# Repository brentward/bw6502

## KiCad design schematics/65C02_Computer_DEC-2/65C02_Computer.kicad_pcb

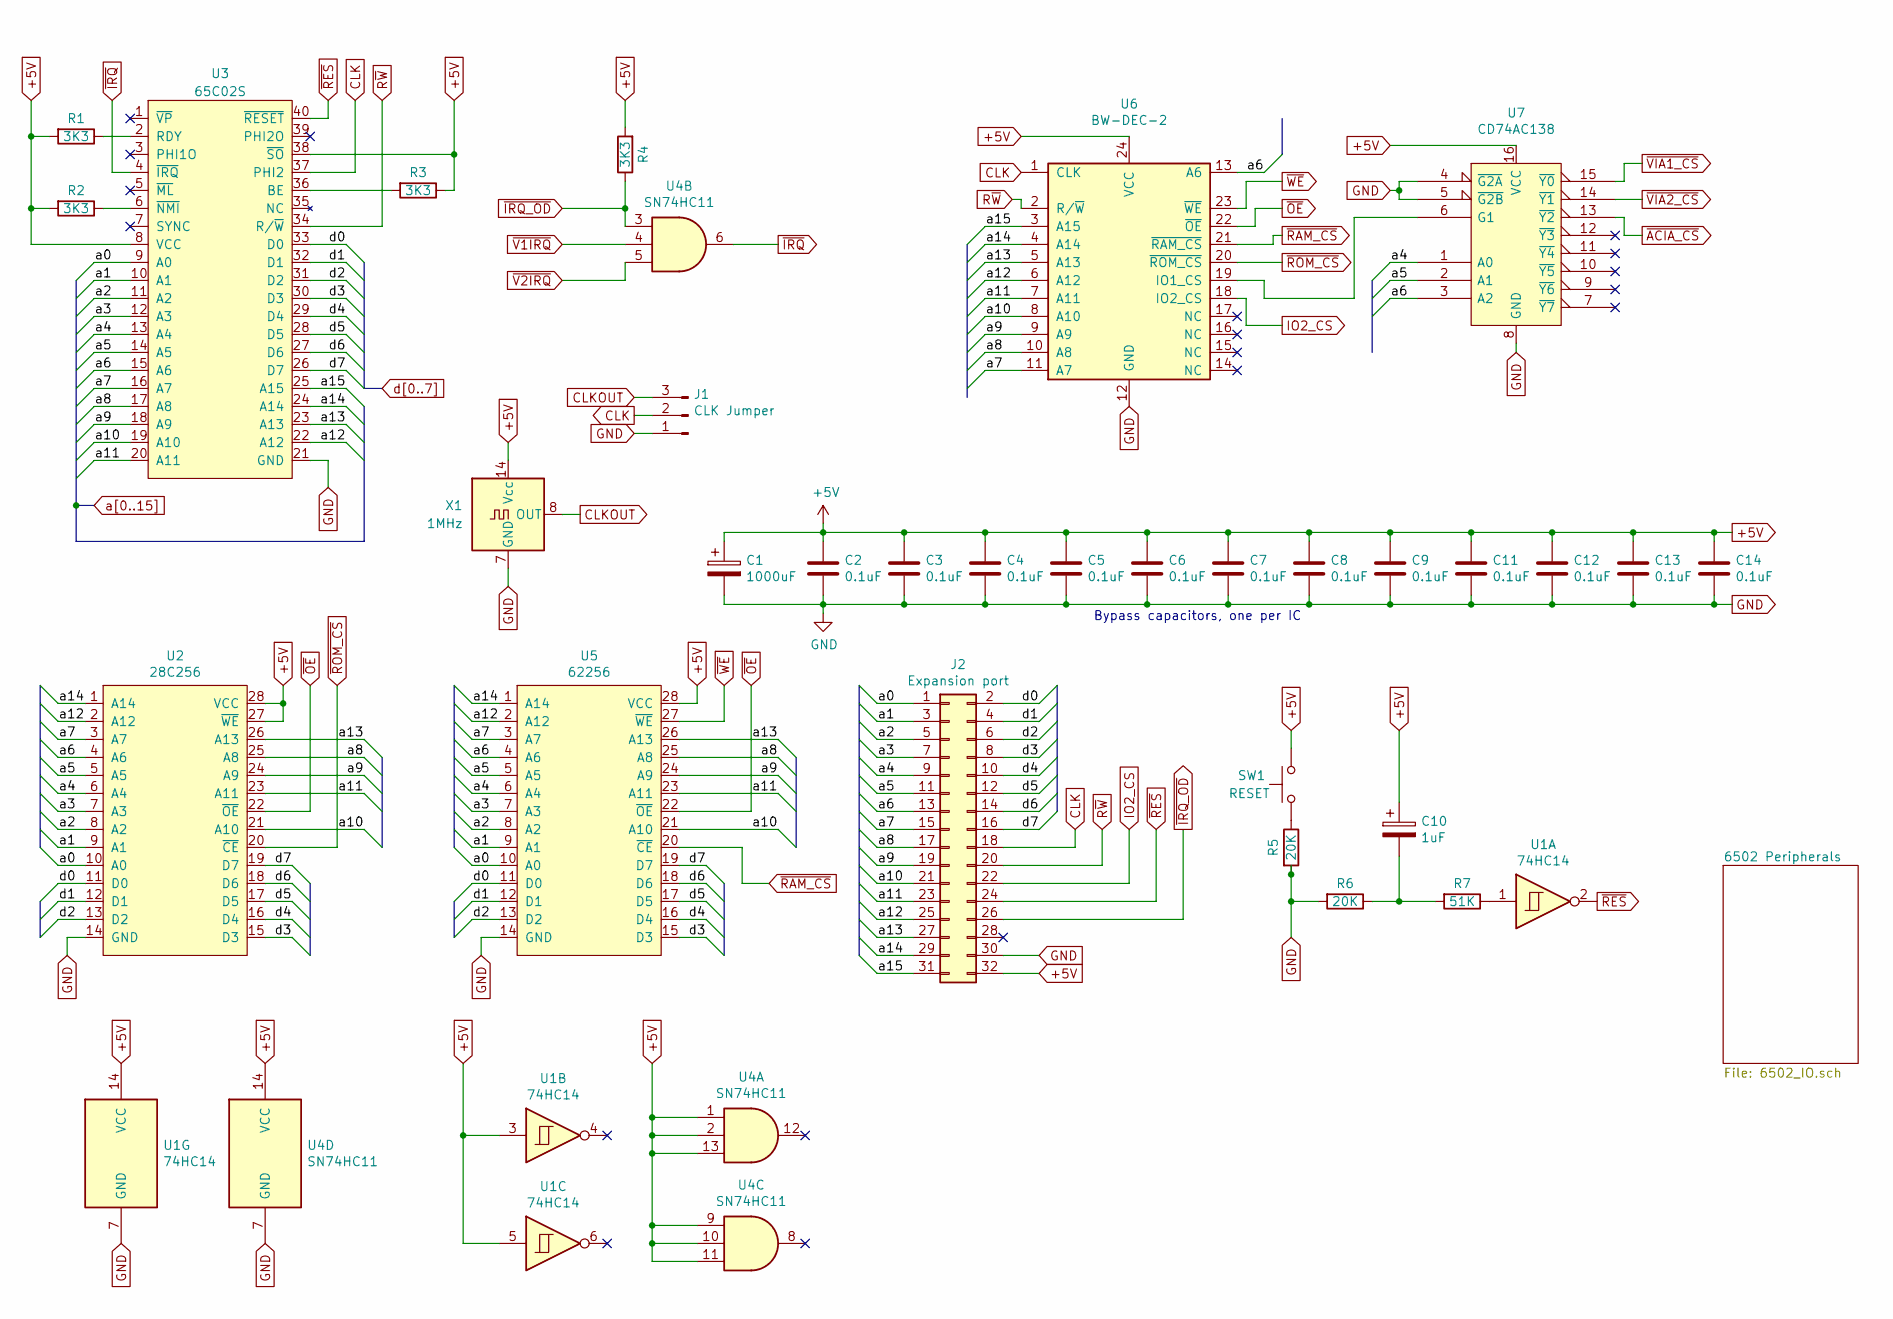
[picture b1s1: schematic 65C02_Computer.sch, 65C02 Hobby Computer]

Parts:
C1: 1000uF; CP_Radial_D10.0mm_P5.00mm
C2, C3, C4, C5, C6, C7, C8, C9, C11, C12, C13, C14: 0.1uF; C_Disc_D3.4mm_W2.1mm_P2.50mm
C10: 1uF; CP_Radial_D5.0mm_P2.50mm
J1: CLK Jumper; PinHeader_1x03_P2.54mm_Vertical
J2: Expansion port; PinSocket_2x16_P2.54mm_Vertical
R1, R2, R3, R4: 3K3; R_Axial_DIN0207_L6.3mm_D2.5mm_P7.62mm_Horizontal
R5, R6: 20K; R_Axial_DIN0207_L6.3mm_D2.5mm_P7.62mm_Horizontal
R7: 51K; R_Axial_DIN0207_L6.3mm_D2.5mm_P7.62mm_Horizontal
SW1: RESET; SW_PUSH_6mm_H4.3mm
U1: 74HC14; DIP-14_W7.62mm
U2: 28C256; DIP-28_W15.24mm_Socket
U3: 65C02S; DIP-40_W15.24mm_Socket
U4: SN74HC11; DIP-14_W7.62mm
U5: 62256; DIP-28_W15.24mm_Socket
U6: BW-DEC-2; DIP-24_W7.62mm_Socket
U7: CD74AC138; DIP-16_W7.62mm
X1: 1MHz; Oscillator_DIP-14

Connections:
+5V: C1.1, C2.1, C3.1, C4.1, C5.1, C6.1, C7.1, C8.1, C9.1, C10.1, C11.1, C12.1, C13.1, C14.1, J2.32, R1.2, R2.2, R3.1, R4.2, SW1.2, U1.3, U1.5, U1.14 (VCC), U2.27 (~WE), U2.28 (VCC), U3.8 (VCC), U3.38 (~SO), U4.1, U4.2, U4.9, U4.10, U4.11, U4.13, U4.14 (VCC), U5.28 (VCC), U6.24 (VCC), U7.16 (VCC), X1.14 (Vcc); also elsewhere on the board
CLK: J1.2, J2.18, U3.37 (PHI2), U6.1 (CLK); also elsewhere on the board
CLKOUT: J1.3, X1.8 (OUT)
GND: C1.2, C2.2, C3.2, C4.2, C5.2, C6.2, C7.2, C8.2, C9.2, C11.2, C12.2, C13.2, C14.2, J1.1, J2.30, R5.2, R6.2, U1.7 (GND), U2.14 (GND), U3.21 (GND), U4.7 (GND), U5.14 (GND), U6.12 (GND), U7.4 (~G2A), U7.5 (~G2B), U7.8 (GND), X1.7 (GND); also elsewhere on the board
IO2_CS: J2.22, U6.18 (IO2_CS)
unnamed: C10.2, R6.1, R7.2
unnamed: R1.1, U3.2 (RDY)
unnamed: R2.1, U3.6 (~NMI)
unnamed: R3.2, U3.36 (BE)
unnamed: R5.1, SW1.1
unnamed: R7.1, U1.1
unnamed: U6.19 (IO1_CS), U7.6 (G1)
R~W: J2.20, U3.34 (R/~W), U6.2 (R/~W); also elsewhere on the board
a0: J2.1, U2.10 (A0), U3.9 (A0), U5.10 (A0); also elsewhere on the board
a1: J2.3, U2.9 (A1), U3.10 (A1), U5.9 (A1); also elsewhere on the board
a2: J2.5, U2.8 (A2), U3.11 (A2), U5.8 (A2); also elsewhere on the board
a3: J2.7, U2.7 (A3), U3.12 (A3), U5.7 (A3); also elsewhere on the board
a4: J2.9, U2.6 (A4), U3.13 (A4), U5.6 (A4), U7.1 (A0)
a5: J2.11, U2.5 (A5), U3.14 (A5), U5.5 (A5), U7.2 (A1)
a6: J2.13, U2.4 (A6), U3.15 (A6), U5.4 (A6), U6.13 (A6), U7.3 (A2)
a7: J2.15, U2.3 (A7), U3.16 (A7), U5.3 (A7), U6.11 (A7)
a8: J2.17, U2.25 (A8), U3.17 (A8), U5.25 (A8), U6.10 (A8)
a9: J2.19, U2.24 (A9), U3.18 (A9), U5.24 (A9), U6.9 (A9)
a10: J2.21, U2.21 (A10), U3.19 (A10), U5.21 (A10), U6.8 (A10)
a11: J2.23, U2.23 (A11), U3.20 (A11), U5.23 (A11), U6.7 (A11)
a12: J2.25, U2.2 (A12), U3.22 (A12), U5.2 (A12), U6.6 (A12)
a13: J2.27, U2.26 (A13), U3.23 (A13), U5.26 (A13), U6.5 (A13)
a14: J2.29, U2.1 (A14), U3.24 (A14), U5.1 (A14), U6.4 (A14)
a15: J2.31, U3.25 (A15), U6.3 (A15)
d0: J2.2, U2.11 (D0), U3.33 (D0), U5.11 (D0); also elsewhere on the board
d1: J2.4, U2.12 (D1), U3.32 (D1), U5.12 (D1); also elsewhere on the board
d2: J2.6, U2.13 (D2), U3.31 (D2), U5.13 (D2); also elsewhere on the board
d3: J2.8, U2.15 (D3), U3.30 (D3), U5.15 (D3); also elsewhere on the board
d4: J2.10, U2.16 (D4), U3.29 (D4), U5.16 (D4); also elsewhere on the board
d5: J2.12, U2.17 (D5), U3.28 (D5), U5.17 (D5); also elsewhere on the board
d6: J2.14, U2.18 (D6), U3.27 (D6), U5.18 (D6); also elsewhere on the board
d7: J2.16, U2.19 (D7), U3.26 (D7), U5.19 (D7); also elsewhere on the board
~ACIA_CS: U7.13 (~Y2); also elsewhere on the board
~IRQ: U3.4 (~IRQ), U4.6
~IRQ_OD: J2.26, R4.1, U4.3; also elsewhere on the board
~OE: U2.22 (~OE), U5.22 (~OE), U6.22 (~OE)
~RAM_CS: U5.20 (~CE), U6.21 (~RAM_CS)
~RES: J2.24, U1.2, U3.40 (~RESET); also elsewhere on the board
~ROM_CS: U2.20 (~CE), U6.20 (~ROM_CS)
~V1IRQ: U4.4; also elsewhere on the board
~V2IRQ: U4.5; also elsewhere on the board
~VIA1_CS: U7.15 (~Y0); also elsewhere on the board
~VIA2_CS: U7.14 (~Y1); also elsewhere on the board
~WE: U5.27 (~WE), U6.23 (~WE)

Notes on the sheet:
Bypass capacitors, one per IC

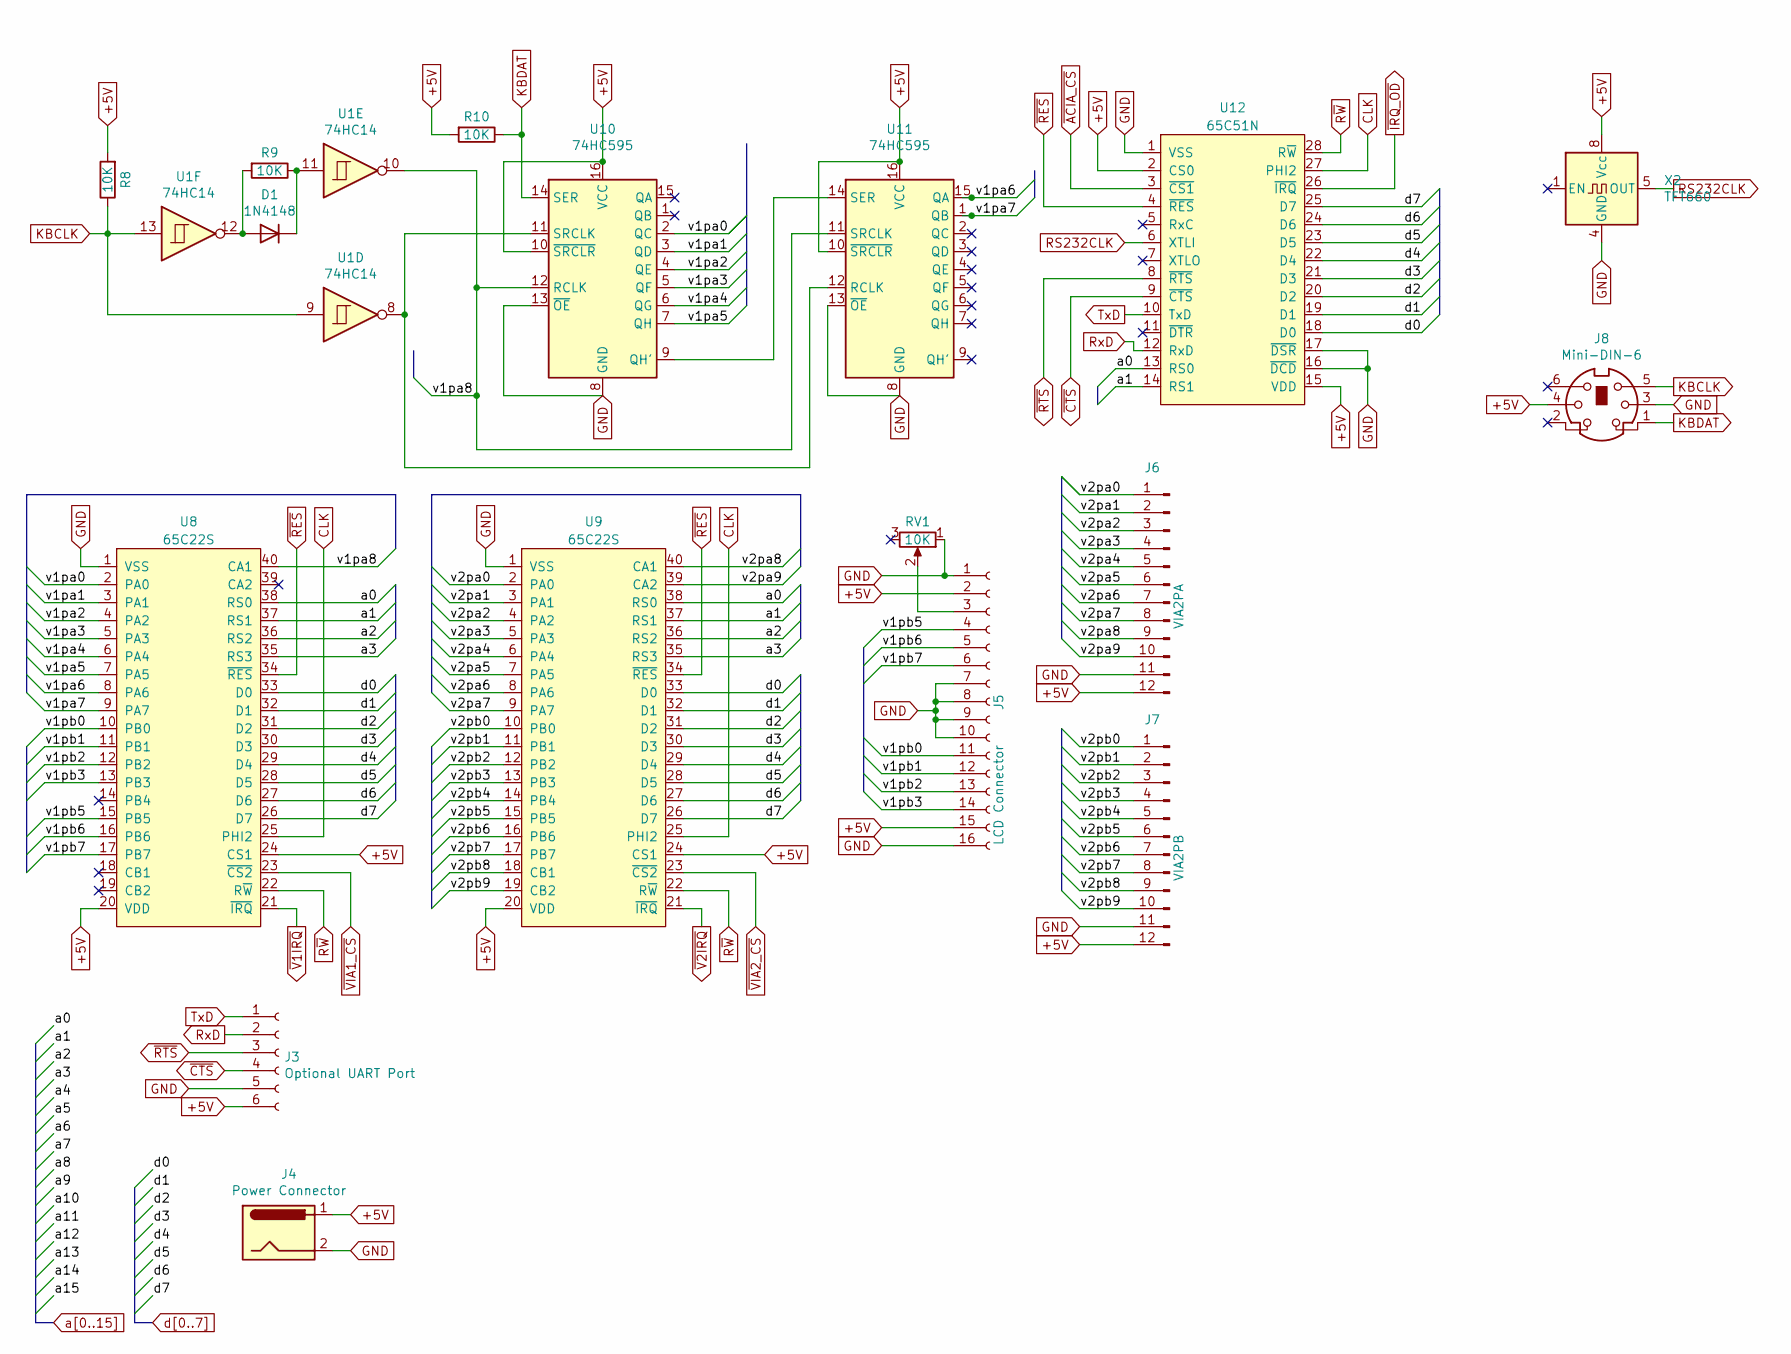
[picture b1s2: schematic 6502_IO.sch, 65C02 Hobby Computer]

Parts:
D1: 1N4148; D_DO-35_SOD27_P7.62mm_Horizontal
J3: Optional UART Port; PinSocket_1x06_P2.54mm_Vertical
J4: Power Connector; BarrelJack_Horizontal
J5: LCD Connector; PinSocket_1x16_P2.54mm_Vertical
J6: VIA2PA; PinHeader_1x12_P2.54mm_Vertical
J7: VIA2PB; PinHeader_1x12_P2.54mm_Vertical
J8: Mini-DIN-6; mini_din-6
R8, R9, R10: 10K; R_Axial_DIN0207_L6.3mm_D2.5mm_P7.62mm_Horizontal
RV1: 10K; Potentiometer_Bourns_3386C_Horizontal
U1: 74HC14; DIP-14_W7.62mm
U8, U9: 65C22S; DIP-40_W15.24mm_Socket
U10, U11: 74HC595; DIP-16_W7.62mm
U12: 65C51N; DIP-28_W15.24mm_Socket
X2: TFT660; Oscillator_DIP-8

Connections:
+5V: J3.6, J4.1, J5.2, J5.15, J6.12, J7.12, J8.4, R8.2, R10.2, U8.20 (VDD), U8.24 (CS1), U9.20 (VDD), U9.24 (CS1), U10.10 (~SRCLR), U10.16 (VCC), U11.10 (~SRCLR), U11.16 (VCC), U12.2 (CS0), U12.15 (VDD), X2.8 (Vcc); also elsewhere on the board
/6502 Peripherals/v1pa0: U8.2 (PA0), U10.2 (QC)
/6502 Peripherals/v1pa1: U8.3 (PA1), U10.3 (QD)
/6502 Peripherals/v1pa2: U8.4 (PA2), U10.4 (QE)
/6502 Peripherals/v1pa3: U8.5 (PA3), U10.5 (QF)
/6502 Peripherals/v1pa4: U8.6 (PA4), U10.6 (QG)
/6502 Peripherals/v1pa5: U8.7 (PA5), U10.7 (QH)
/6502 Peripherals/v1pa6: U8.8 (PA6), U11.15 (QA)
/6502 Peripherals/v1pa7: U8.9 (PA7), U11.1 (QB)
/6502 Peripherals/v1pa8: U1.10, U8.40 (CA1), U10.12 (RCLK), U11.11 (SRCLK)
/6502 Peripherals/v1pb0: J5.11, U8.10 (PB0)
/6502 Peripherals/v1pb1: J5.12, U8.11 (PB1)
/6502 Peripherals/v1pb2: J5.13, U8.12 (PB2)
/6502 Peripherals/v1pb3: J5.14, U8.13 (PB3)
/6502 Peripherals/v1pb5: J5.4, U8.15 (PB5)
/6502 Peripherals/v1pb6: J5.5, U8.16 (PB6)
/6502 Peripherals/v1pb7: J5.6, U8.17 (PB7)
/6502 Peripherals/v2pa0: J6.1, U9.2 (PA0)
/6502 Peripherals/v2pa1: J6.2, U9.3 (PA1)
/6502 Peripherals/v2pa2: J6.3, U9.4 (PA2)
/6502 Peripherals/v2pa3: J6.4, U9.5 (PA3)
/6502 Peripherals/v2pa4: J6.5, U9.6 (PA4)
/6502 Peripherals/v2pa5: J6.6, U9.7 (PA5)
/6502 Peripherals/v2pa6: J6.7, U9.8 (PA6)
/6502 Peripherals/v2pa7: J6.8, U9.9 (PA7)
/6502 Peripherals/v2pa8: J6.9, U9.40 (CA1)
/6502 Peripherals/v2pa9: J6.10, U9.39 (CA2)
/6502 Peripherals/v2pb0: J7.1, U9.10 (PB0)
/6502 Peripherals/v2pb1: J7.2, U9.11 (PB1)
/6502 Peripherals/v2pb2: J7.3, U9.12 (PB2)
/6502 Peripherals/v2pb3: J7.4, U9.13 (PB3)
/6502 Peripherals/v2pb4: J7.5, U9.14 (PB4)
/6502 Peripherals/v2pb5: J7.6, U9.15 (PB5)
/6502 Peripherals/v2pb6: J7.7, U9.16 (PB6)
/6502 Peripherals/v2pb7: J7.8, U9.17 (PB7)
/6502 Peripherals/v2pb8: J7.9, U9.18 (CB1)
/6502 Peripherals/v2pb9: J7.10, U9.19 (CB2)
CLK: U8.25 (PHI2), U9.25 (PHI2), U12.27 (PHI2); also elsewhere on the board
GND: J3.5, J4.2, J5.1, J5.7, J5.8, J5.9, J5.10, J5.16, J6.11, J7.11, J8.3, RV1.1, U8.1 (VSS), U9.1 (VSS), U10.8 (GND), U10.13 (~OE), U11.8 (GND), U11.13 (~OE), U12.1 (VSS), U12.16 (~DCD), U12.17 (~DSR), X2.4 (GND); also elsewhere on the board
KBCLK: J8.5, R8.1, U1.9, U1.13
KBDAT: J8.1, R10.1, U10.14 (SER)
unnamed: D1.1 (K), R9.1, U1.11
unnamed: D1.2 (A), R9.2, U1.12
unnamed: J5.3, RV1.2
unnamed: U1.8, U10.11 (SRCLK), U11.12 (RCLK)
unnamed: U10.9 (QH'), U11.14 (SER)
RS232CLK: U12.6 (XTLI), X2.5 (OUT)
RxD: J3.2, U12.12 (RxD)
R~W: U8.22 (R~W), U9.22 (R~W), U12.28 (R~W); also elsewhere on the board
TxD: J3.1, U12.10 (TxD)
a0: U8.38 (RS0), U9.38 (RS0), U12.13 (RS0); also elsewhere on the board
a1: U8.37 (RS1), U9.37 (RS1), U12.14 (RS1); also elsewhere on the board
a2: U8.36 (RS2), U9.36 (RS2); also elsewhere on the board
a3: U8.35 (RS3), U9.35 (RS3); also elsewhere on the board
d0: U8.33 (D0), U9.33 (D0), U12.18 (D0); also elsewhere on the board
d1: U8.32 (D1), U9.32 (D1), U12.19 (D1); also elsewhere on the board
d2: U8.31 (D2), U9.31 (D2), U12.20 (D2); also elsewhere on the board
d3: U8.30 (D3), U9.30 (D3), U12.21 (D3); also elsewhere on the board
d4: U8.29 (D4), U9.29 (D4), U12.22 (D4); also elsewhere on the board
d5: U8.28 (D5), U9.28 (D5), U12.23 (D5); also elsewhere on the board
d6: U8.27 (D6), U9.27 (D6), U12.24 (D6); also elsewhere on the board
d7: U8.26 (D7), U9.26 (D7), U12.25 (D7); also elsewhere on the board
~ACIA_CS: U12.3 (~CS1); also elsewhere on the board
~CTS: J3.4, U12.9 (~CTS)
~IRQ_OD: U12.26 (~IRQ); also elsewhere on the board
~RES: U8.34 (~RES), U9.34 (~RES), U12.4 (~RES); also elsewhere on the board
~RTS: J3.3, U12.8 (~RTS)
~V1IRQ: U8.21 (~IRQ); also elsewhere on the board
~V2IRQ: U9.21 (~IRQ); also elsewhere on the board
~VIA1_CS: U8.23 (~CS2); also elsewhere on the board
~VIA2_CS: U9.23 (~CS2); also elsewhere on the board

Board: 2 copper layers, 49 parts (0 on the bottom side), 97 nets, no tracks yet.

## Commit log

2021-05-03 Adding backspace, esc to clear, and enter handing. Reorganizing code.
2021-05-03 fixing .gitignore to match new dir structure
2021-05-03 removing .python-version
2021-05-03 LED testing for VIA2
2021-05-04 added handling for multi byte ps2 scancodes
2021-05-06 Adding code for PLD memory decoders
2021-05-06 Changing device to fix fuse count of .jed files
2021-05-07 Fixing errors in DEC code
2021-05-07 cleanup of DEC code
2021-05-07 fixing errors from bad save
2021-05-07 Restoring polarity optimization compilation flag
2021-05-08 adding datasheets to repo
2021-05-10 New schematic plus missing datasheet
2021-05-10 removing Mac OS files from repo
2021-05-10 Updating new schematic for BW-DEC-2
2021-05-11 schematics for computer with BW-DEC-2
2021-05-11 Address changes to VIAs and variables to account for new address space with BW-DEC-2 address decoder
2021-05-13 fixing comments to match current address ranges
2021-05-14 Addig code for UART on ACIA chip
2021-05-14 Restting the ACIA status register on init
2021-05-14 Working transmit
2021-05-18 Adding basic, EhBASIC is working
2021-05-21 Working C02Monitor and C02BIOS
2021-05-21 C02Monitor and C02Basic with attempting keyboard driver
2021-05-21 Working input buffer for keyboard and serial
2021-05-23 working circular input buffer shared between serial in and keyboard
2021-05-26 handle ctrl + key
2021-06-13 adding datasheets
